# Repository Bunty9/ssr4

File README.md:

<div align="center">

# SSR4

**An open-source, four-channel 230 VAC solid-state switch for Home Assistant.**<br>
ESP32-C3 · ESPHome · zero-cross SSRs · hardware over-temperature cutoff · KiCad 10

</div>

> [!WARNING]
> **This board switches mains voltage, which can kill.** Build, test and install it only if you
> are competent to work on 230 V wiring, follow the [safety guide](docs/safety.md), and keep
> the board disconnected from mains while flashing or handling it. It is an **uncertified
> prototype design**, provided as is, without warranty.

## What it is

SSR4 turns four ordinary 230 V circuits (ceiling fans, LED lights) into Home Assistant switches.
It is small enough (90 × 75 mm) to sit in a 3D-printed case inside a wall switchboard, runs
[ESPHome](https://esphome.io) on an ESP32-C3, and works entirely on your local network.

It was designed to be **safe by construction, not by firmware**:

- **Every output turns off by itself when the board overheats.** A 60 °C temperature switch cuts
  the drive of all four SSRs in hardware, with no software in the path. The firmware adds an
  earlier 55 °C cutoff, a sensor-fault check and reporting.
- **Every output is OFF at power-up and after any reset**, enforced by gate pull-downs sized
  against the microcontroller's own reset pull-ups, before the firmware even runs, and never
  restored automatically after a power cut.
- **Mains and low voltage are 6.5 mm apart** on every layer (reinforced isolation spacing),
  checked by KiCad DRC rules shipped with the design.
- **Each channel is fused** (2 A time-lag) and has its own terminals, so the board never carries
  the sum of the loads.
- **Flash and test it from USB-C with mains disconnected**: the logic runs from USB alone.

## Gallery

| | |
|:---:|:---:|
|  |  |
| Top: mains along the upper edge, low voltage below | The terminal side: per-channel L_IN / L_OUT pairs |
|  |  |
| U7, the 60 °C hardware cutoff, sits between the SSRs | A scouter on the silkscreen: power level well over 9000 |

Full-resolution renders (4K) are in [`docs/images/`](docs/images/). The schematic and the copper
layers are in [`hardware/ssr4-schematic.pdf`](hardware/ssr4-schematic.pdf) and
[`hardware/ssr4-pcb-layers.pdf`](hardware/ssr4-pcb-layers.pdf).

## Specifications

| | |
|---|---|
| Outputs | 4 × 230 VAC, zero-cross triac SSR (Littelfuse/IXYS CPC40055ST, 20-280 Vrms, 2500 Vrms isolation) |
| Load per channel | below 1 A continuous (LED lights, fans); 2 A time-lag fuse per channel |
| Supply | 230 VAC via an isolated 5 V / 3 W module (HLK-PM01) with fuse and varistor, or USB-C 5 V for flashing |
| Controller | ESP32-C3-MINI-1 (RISC-V, Wi-Fi, 4 MB flash), native USB-C (Serial/JTAG) with ESD protection |
| Protection | hardware cutoff 60 °C ± 2 °C (TMP302, releases ~50 °C); firmware cutoff 55 °C / resume 45 °C, also latched by a hardware trip; NTC fault detection; fail-safe OFF |
| Indicators | one LED per channel, status LED |
| Board | 90 × 75 mm, 2 layers, 1.6 mm, 2 oz copper, 67 parts, four M3 holes |
| Firmware | ESPHome 2026.10 (ESP-IDF): encrypted Home Assistant API, password-protected OTA, captive-portal setup |

## From zero to switching lights

| Step | Guide |
|---|---|
| 1. Understand the board | [How it works](docs/how-it-works.md) · [Safety](docs/safety.md) |
| 2. Order it assembled (JLCPCB or PCBWay) or build it yourself | [Fabrication](docs/fabrication.md) |
| 3. Flash ESPHome over USB-C and add it to Home Assistant | [Firmware](docs/firmware.md) |
| 4. Bring it up step by step: USB, thermal checks, 24 VAC loads, first mains | [Bring-up](docs/bring-up.md) |
| 5. Wire it into a switchboard | [Installation](docs/installation.md) |
| 5b. Design a heat sink and an enclosure (STEP files included) | [Mechanical](docs/mechanical.md) |
| 6. Change it, test it, contribute | [Development](docs/development.md) · [Contributing](CONTRIBUTING.md) |

## How it has been checked

Nothing here has been built yet: rev A is a **gated, unbuilt design**. Every published file was
produced by a pipeline that refuses to release a board until its checks pass. The results of
this snapshot are in [`validation/`](validation/README.md):

| Check | Result |
|---|---|
| Datasheet pinouts: every IC, transistor, diode and connector pin extracted twice, independently, and compared | 11 parts verified, 0 disagreements left |
| Netlist tests: safety and correctness properties proved on the generated schematic | 16 passed |
| ERC | 0 errors |
| DRC, including the mains clearance and creepage rules | 0 errors, 0 unconnected (24 silkscreen warnings) |
| Fabrication rules (JLCPCB) and the order package | pass |
| Firmware behaviour on a PC simulation of the board (14 tests) | 14 passed |
| Independent design review of the final layout | 1 high and 7 medium findings: the safety-relevant ones fixed before publishing, the rest listed |
| NTC divider: closed-form design maths vs an ngspice simulation | agree within the simulator's tolerance |

Bench validation of a real board (thermal, EMC, trip points) is the next step. If you build
one, please [send a build report](https://github.com/Bunty9/ssr4/issues/new/choose).

## What it costs

About **$106 per board in parts** (5 boards, JLCPCB prices of October 2026), before PCB,
assembly and shipping. The four SSRs are $97 of that; everything else is under $9. The
[fabrication guide](docs/fabrication.md#what-it-costs) has the breakdown and a cheaper-variant
idea.

## Home Assistant

The board appears as an ESPHome device with four switches (**Channel 1-4**), the **SSR
temperature**, and three protection states: **Over-temperature**, **NTC fault** and **Hardware
over-temperature cutoff**. A channel refuses to turn on while any protection is active, so the
dashboard always shows what the hardware is really doing.

## Repository layout

```
hardware/      KiCad 10 project, libraries, circuit source (Python), fabrication files, pinouts, PDFs,
               mechanical/ (STEP assembly, board STEP, outline DXF)
firmware/      ESPHome configuration (board + PC simulation), generated pin map, tests
fwtest/        labgrid-based test harness used by the firmware tests
validation/    test results, calculations, SPICE cross-check of this snapshot
docs/          guides and full-resolution renders
```

## Contributing

Build reports, bug reports and improvements are welcome. Read [CONTRIBUTING.md](CONTRIBUTING.md)
first; safety problems go to the private channel in [SECURITY.md](SECURITY.md). This project
follows the [Contributor Covenant](CODE_OF_CONDUCT.md).

## License

- Hardware: [CERN-OHL-S-2.0](LICENSES/CERN-OHL-S-2.0.txt)
- Firmware and software: [MIT](LICENSES/MIT.txt)
- Documentation and images: [CC BY-SA 4.0](LICENSES/CC-BY-SA-4.0.txt)

Details and credits (including the scouter doodle, after fan art by camarinox; Dragon Ball ©
Bird Studio/Shueisha, Toei Animation) in [LICENSES/README.md](LICENSES/README.md).

<sub>Published from source commit `4ecfc79` on 2026-10-29.</sub>

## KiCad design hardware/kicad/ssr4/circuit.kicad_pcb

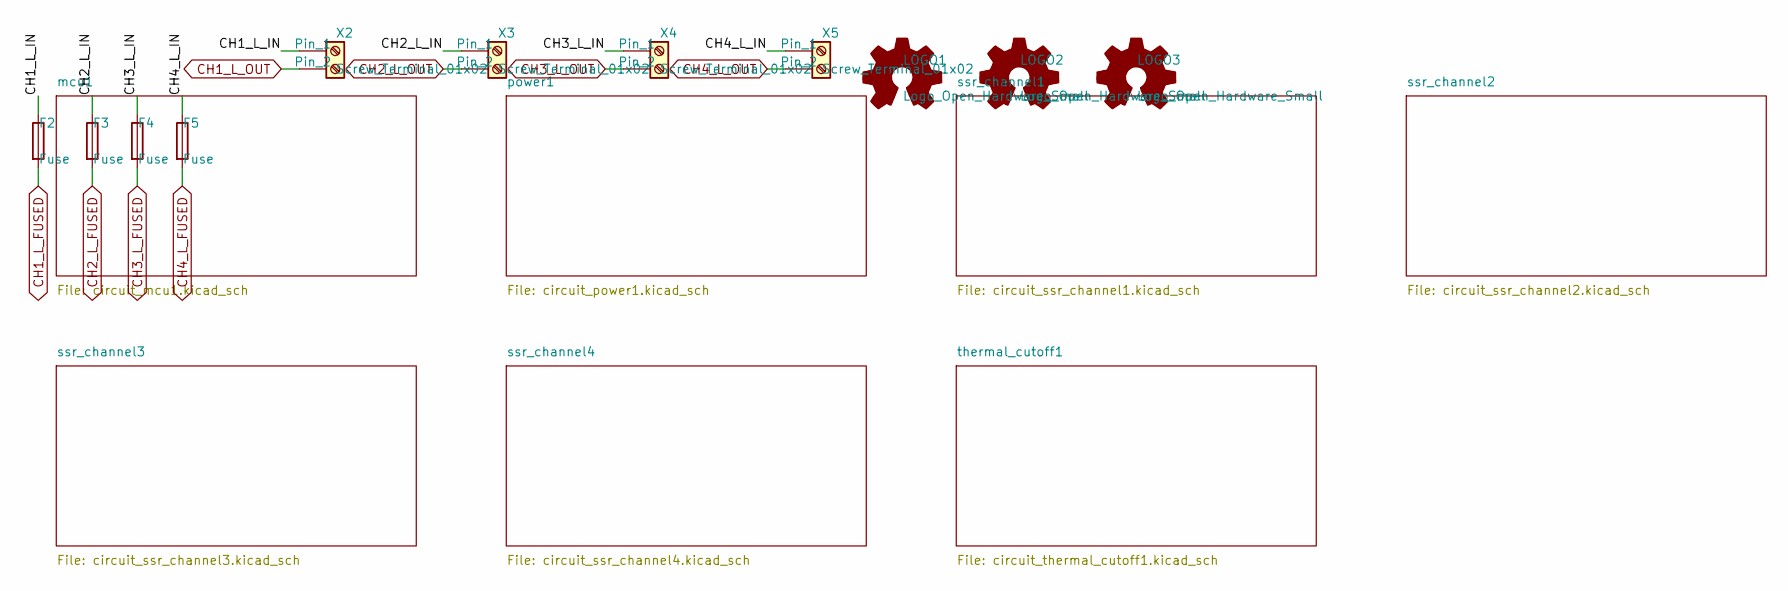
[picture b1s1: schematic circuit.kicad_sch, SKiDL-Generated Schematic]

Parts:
F2, F3, F4, F5: Fuse; Fuse_Littelfuse_395Series; MPN 39212000000; LCSC C142678
LOGO1: Logo_Open_Hardware_Small; Label_MainsWarning; MPN UNSET-MPN
LOGO2: Logo_Open_Hardware_Small; Doodle_Scouter; MPN UNSET-MPN
LOGO3: Logo_Open_Hardware_Small; Label_Terminals; MPN UNSET-MPN
X2, X3, X4, X5: Screw_Terminal_01x02; TerminalBlock_CUI_TB007-508-02_1x02_P5.08mm_Horizontal; MPN WJ500V-5.08-2P; LCSC C8465

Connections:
/CH1_L_IN: F2.1, X2.1
/CH2_L_IN: F3.1, X3.1
/CH3_L_IN: F4.1, X4.1
/CH4_L_IN: F5.1, X5.1
CH1_L_FUSED: F2.2; also elsewhere on the board
CH1_L_OUT: X2.2; also elsewhere on the board
CH2_L_FUSED: F3.2; also elsewhere on the board
CH2_L_OUT: X3.2; also elsewhere on the board
CH3_L_FUSED: F4.2; also elsewhere on the board
CH3_L_OUT: X4.2; also elsewhere on the board
CH4_L_FUSED: F5.2; also elsewhere on the board
CH4_L_OUT: X5.2; also elsewhere on the board

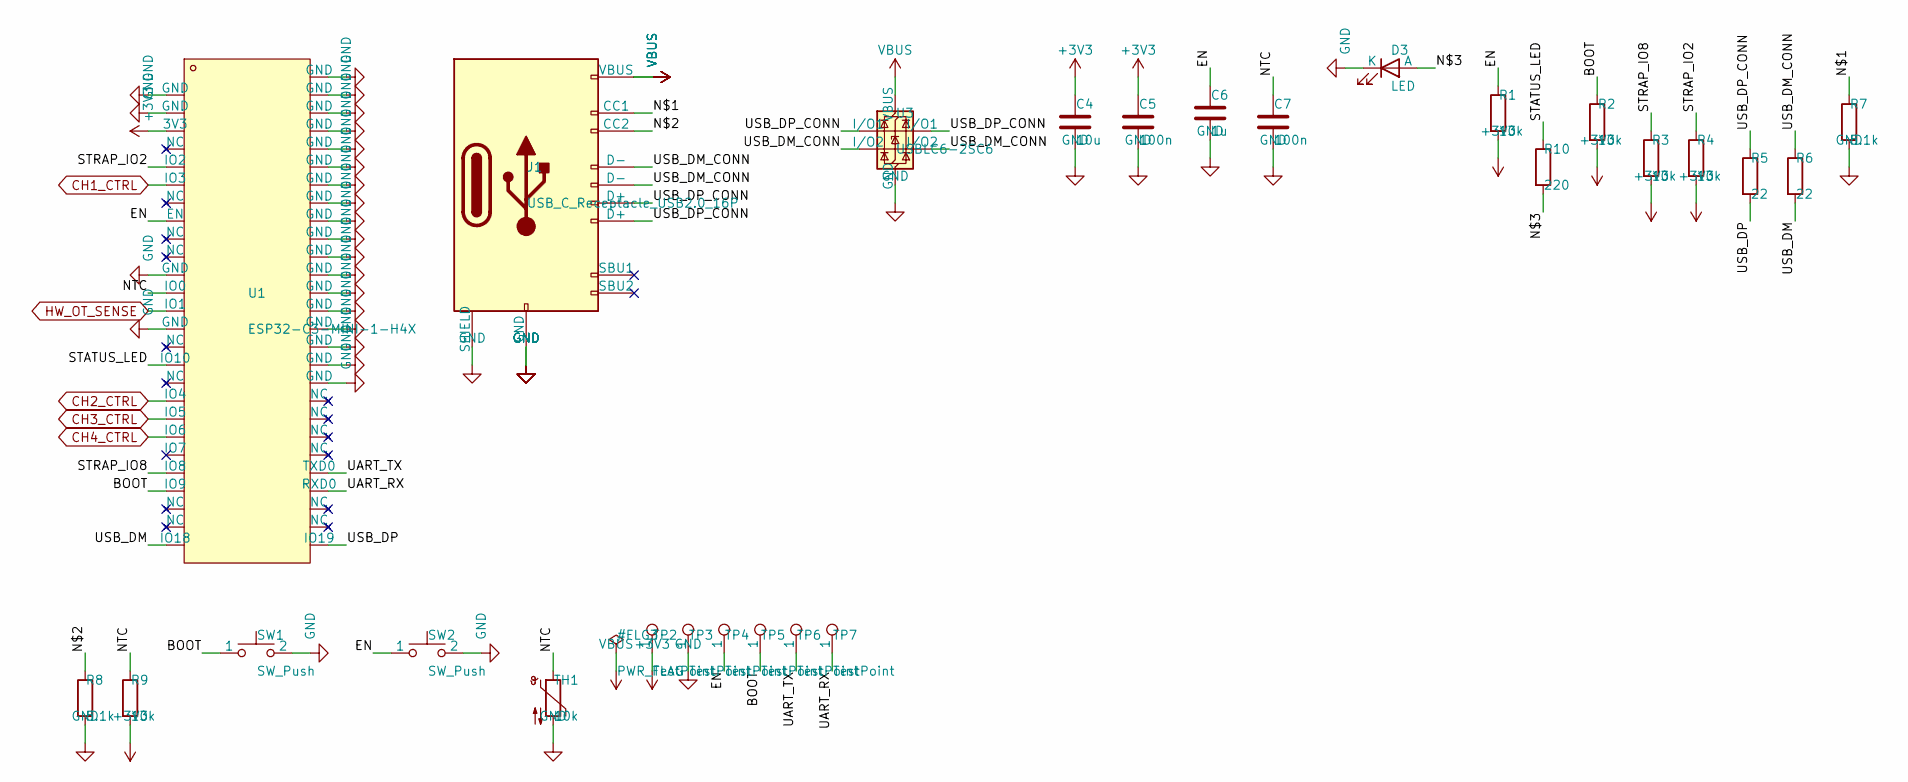
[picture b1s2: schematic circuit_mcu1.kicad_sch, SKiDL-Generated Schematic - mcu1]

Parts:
C4: 10u; C_0603_1608Metric; MPN CL10A106MA8NRNC; LCSC C96446
C5, C7: 100n; C_0402_1005Metric; MPN CL05B104KO5NNNC; LCSC C1525
C6: 1u; C_0402_1005Metric; MPN CL05A105KA5NQNC; LCSC C52923
D3: LED; LED_0603_1608Metric; MPN 19-217/R6C-AL1M2VY/6T; LCSC C2986060
J1: USB_C_Receptacle_USB2.0_16P; USB_C_Receptacle_HRO_TYPE-C-31-M-12; MPN TYPE-C-31-M-12; LCSC C165948
R1, R2, R3, R4, R9: 10k; R_0402_1005Metric; MPN 0402WGF1002TCE; LCSC C25744
R5, R6: 22; R_0402_1005Metric; MPN 0402WGF220JTCE; LCSC C25092
R7, R8: 5.1k; R_0402_1005Metric; MPN 0402WGF5101TCE; LCSC C25905
R10: 220; R_0402_1005Metric; MPN 0402WGF2200TCE; LCSC C25091
SW1, SW2: SW_Push; SW_Push_1P1T_XKB_TS-1187A; MPN TS-1187A-B-A-B; LCSC C318884
TH1: 10k; R_0603_1608Metric; MPN SDNT1608X103F3950FTF; LCSC C279936
TP2, TP3, TP4, TP5, TP6, TP7: TestPoint; TestPoint_Pad_D1.5mm; MPN UNSET-MPN
U1: ESP32-C3-MINI-1-H4X; WIFIM-SMD_ESP32-C3-MINI-1; MPN ESP32-C3-MINI-1-H4X; LCSC C41349510
U3: USBLC6-2SC6; SOT-23-6; MPN USBLC6-2SC6; LCSC C7519

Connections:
+3V3: C4.1, C5.1, R1.2, R2.2, R3.2, R4.2, R9.2, TP2.1, U1.3 (3V3); also elsewhere on the board
/mcu1/BOOT: R2.1, SW1.1, TP5.1, U1.23 (IO9)
/mcu1/EN: C6.1, R1.1, SW2.1, TP4.1, U1.8 (EN)
/mcu1/N$1: J1.A5 (CC1), R7.1
/mcu1/N$2: J1.B5 (CC2), R8.1
/mcu1/N$3: D3.2 (A), R10.2
/mcu1/NTC: C7.1, R9.1, TH1.1, U1.12 (IO0)
/mcu1/STATUS_LED: R10.1, U1.16 (IO10)
/mcu1/STRAP_IO2: R4.1, U1.5 (IO2)
/mcu1/STRAP_IO8: R3.1, U1.22 (IO8)
/mcu1/UART_RX: TP7.1, U1.30 (RXD0)
/mcu1/UART_TX: TP6.1, U1.31 (TXD0)
/mcu1/USB_DM: R6.2, U1.26 (IO18)
/mcu1/USB_DM_CONN: J1.A7 (D-), J1.B7 (D-), R6.1, U3.3 (I/O2), U3.4 (I/O2)
/mcu1/USB_DP: R5.2, U1.27 (IO19)
/mcu1/USB_DP_CONN: J1.A6 (D+), J1.B6 (D+), R5.1, U3.1 (I/O1), U3.6 (I/O1)
CH1_CTRL: U1.6 (IO3); also elsewhere on the board
CH2_CTRL: U1.18 (IO4); also elsewhere on the board
CH3_CTRL: U1.19 (IO5); also elsewhere on the board
CH4_CTRL: U1.20 (IO6); also elsewhere on the board
GND: C4.2, C5.2, C6.2, C7.2, D3.1 (K), J1.A1 (GND), J1.A12 (GND), J1.B1 (GND), J1.B12 (GND), J1.SH (SHIELD), R7.2, R8.2, SW1.2, SW2.2, TH1.2, TP3.1, U1.1 (GND), U1.2 (GND), U1.11 (GND), U1.14 (GND), U1.36 (GND), U1.37 (GND), U1.38 (GND), U1.39 (GND), U1.40 (GND), U1.41 (GND), U1.42 (GND), U1.43 (GND), U1.44 (GND), U1.45 (GND), U1.46 (GND), U1.47 (GND), U1.48 (GND), U1.49 (GND), U1.50 (GND), U1.51 (GND), U1.52 (GND), U1.53 (GND), U3.2 (GND); also elsewhere on the board
HW_OT_SENSE: U1.13 (IO1); also elsewhere on the board
VBUS: J1.A4 (VBUS), J1.A9 (VBUS), J1.B4 (VBUS), J1.B9 (VBUS), U3.5 (VBUS); also elsewhere on the board

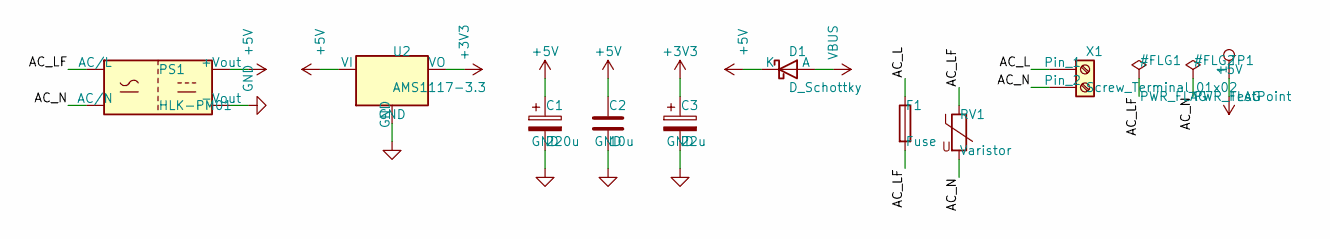
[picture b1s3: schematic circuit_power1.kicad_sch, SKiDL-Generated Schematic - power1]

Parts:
C1: 220u; CP_Elec_6.3x5.4; MPN RVT1C221M0605; LCSC C2977551
C2: 10u; C_0603_1608Metric; MPN CL10A106MA8NRNC; LCSC C96446
C3: 22u; CP_EIA-3528-21_Kemet-B; MPN CA45-B016K226T; LCSC C122226
D1: D_Schottky; D_SOD-123; MPN B5819W SL; LCSC C8598
F1: Fuse; Fuse_Littelfuse_395Series; MPN 39211000000; LCSC C99566
PS1: HLK-PM01; Converter_ACDC_Hi-Link_HLK-PMxx; MPN HLK-PM01; LCSC C209903
RV1: Varistor; RV_Disc_D12mm_W6.7mm_P7.5mm; MPN 10D561K; LCSC C2839517
TP1: TestPoint; TestPoint_Pad_D1.5mm; MPN UNSET-MPN
U2: AMS1117-3.3; SOT-223-3_TabPin2; MPN AMS1117-3.3; LCSC C6186
X1: Screw_Terminal_01x02; TerminalBlock_CUI_TB007-508-02_1x02_P5.08mm_Horizontal; MPN WJ500V-5.08-2P; LCSC C8465

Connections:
+3V3: C3.1, U2.2 (VO); also elsewhere on the board
+5V: C1.1, C2.1, D1.1 (K), PS1.4 (+Vout), TP1.1, U2.3 (VI); also elsewhere on the board
/power1/AC_L: F1.1, X1.1
/power1/AC_LF: F1.2, PS1.1 (AC/L), RV1.1
/power1/AC_N: PS1.2 (AC/N), RV1.2, X1.2
GND: C1.2, C2.2, C3.2, PS1.3 (-Vout), U2.1 (GND); also elsewhere on the board
VBUS: D1.2 (A); also elsewhere on the board

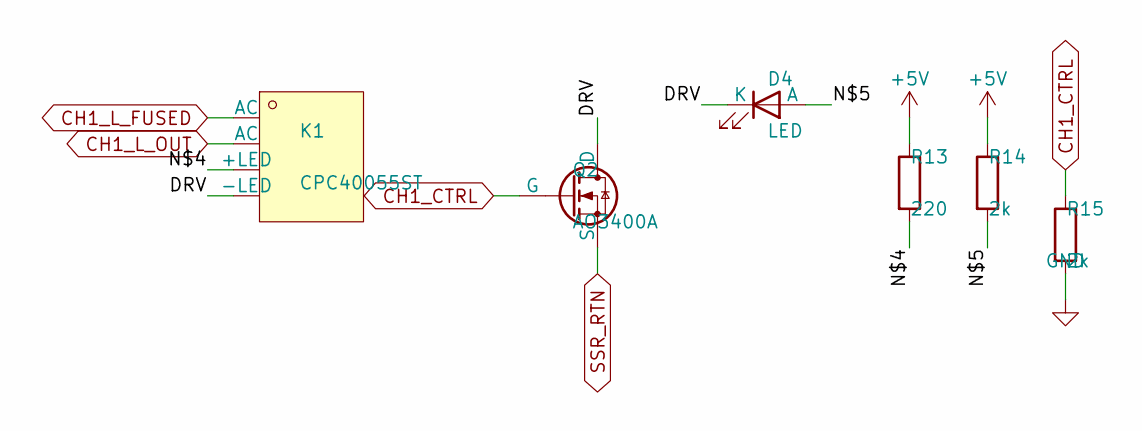
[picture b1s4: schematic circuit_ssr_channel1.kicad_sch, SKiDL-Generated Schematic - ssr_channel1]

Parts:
D4: LED; LED_0603_1608Metric; MPN 19-217/R6C-AL1M2VY/6T; LCSC C2986060
K1: CPC40055ST; SIP-4_L38.1-W3.8_CPC40055ST; MPN CPC40055ST; LCSC C1527353
Q2: AO3400A; SOT-23; MPN AO3400A; LCSC C20917
R13: 220; R_1206_3216Metric; MPN 1206W4F2200T5E; LCSC C17957
R14, R15: 2k; R_0402_1005Metric; MPN 0402WGF2001TCE; LCSC C4109

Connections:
+5V: R13.1, R14.1; also elsewhere on the board
/ssr_channel1/DRV: D4.1 (K), K1.4 (-LED), Q2.3 (D)
/ssr_channel1/N$4: K1.3 (+LED), R13.2
/ssr_channel1/N$5: D4.2 (A), R14.2
CH1_CTRL: Q2.1 (G), R15.1; also elsewhere on the board
CH1_L_FUSED: K1.1 (AC); also elsewhere on the board
CH1_L_OUT: K1.2 (AC); also elsewhere on the board
GND: R15.2; also elsewhere on the board
SSR_RTN: Q2.2 (S); also elsewhere on the board

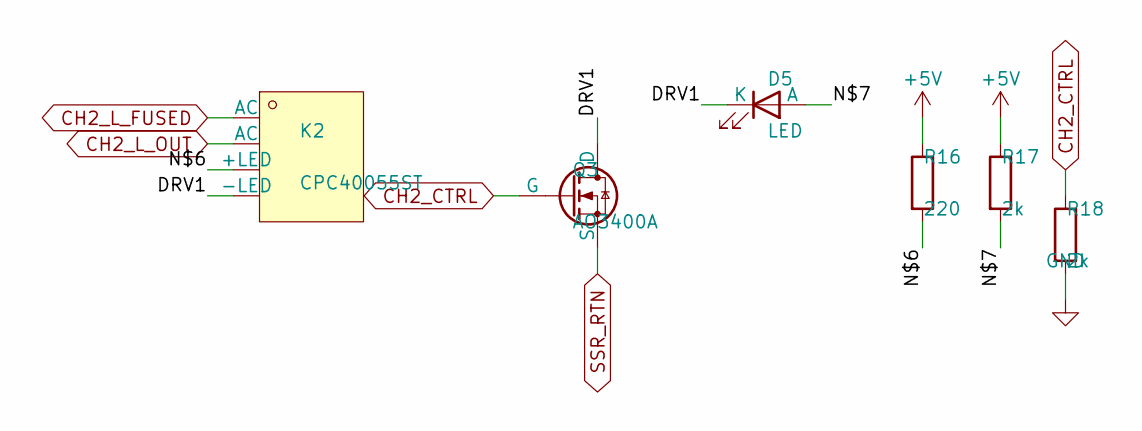
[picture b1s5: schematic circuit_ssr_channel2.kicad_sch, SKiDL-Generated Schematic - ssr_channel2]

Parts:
D5: LED; LED_0603_1608Metric; MPN 19-217/R6C-AL1M2VY/6T; LCSC C2986060
K2: CPC40055ST; SIP-4_L38.1-W3.8_CPC40055ST; MPN CPC40055ST; LCSC C1527353
Q3: AO3400A; SOT-23; MPN AO3400A; LCSC C20917
R16: 220; R_1206_3216Metric; MPN 1206W4F2200T5E; LCSC C17957
R17, R18: 2k; R_0402_1005Metric; MPN 0402WGF2001TCE; LCSC C4109

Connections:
+5V: R16.1, R17.1; also elsewhere on the board
/ssr_channel2/DRV1: D5.1 (K), K2.4 (-LED), Q3.3 (D)
/ssr_channel2/N$6: K2.3 (+LED), R16.2
/ssr_channel2/N$7: D5.2 (A), R17.2
CH2_CTRL: Q3.1 (G), R18.1; also elsewhere on the board
CH2_L_FUSED: K2.1 (AC); also elsewhere on the board
CH2_L_OUT: K2.2 (AC); also elsewhere on the board
GND: R18.2; also elsewhere on the board
SSR_RTN: Q3.2 (S); also elsewhere on the board

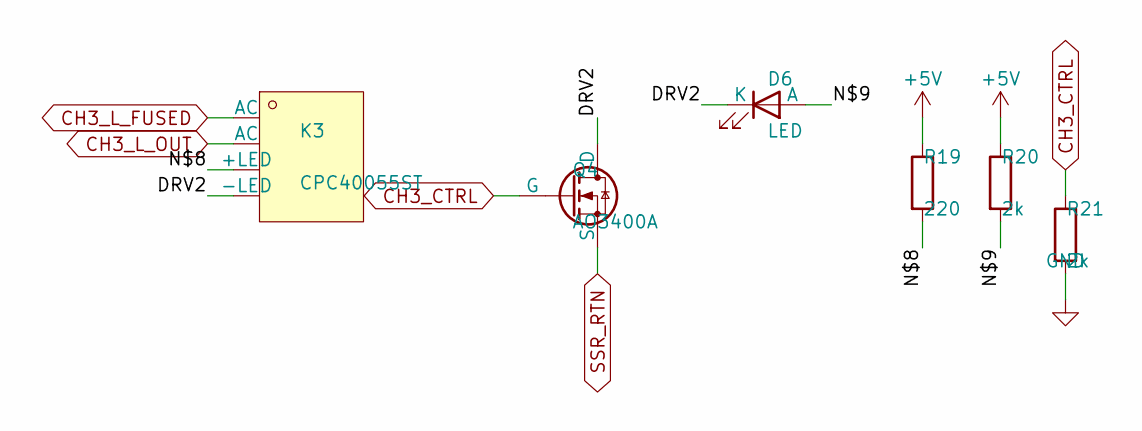
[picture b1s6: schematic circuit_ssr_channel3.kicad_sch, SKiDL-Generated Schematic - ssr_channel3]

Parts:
D6: LED; LED_0603_1608Metric; MPN 19-217/R6C-AL1M2VY/6T; LCSC C2986060
K3: CPC40055ST; SIP-4_L38.1-W3.8_CPC40055ST; MPN CPC40055ST; LCSC C1527353
Q4: AO3400A; SOT-23; MPN AO3400A; LCSC C20917
R19: 220; R_1206_3216Metric; MPN 1206W4F2200T5E; LCSC C17957
R20, R21: 2k; R_0402_1005Metric; MPN 0402WGF2001TCE; LCSC C4109

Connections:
+5V: R19.1, R20.1; also elsewhere on the board
/ssr_channel3/DRV2: D6.1 (K), K3.4 (-LED), Q4.3 (D)
/ssr_channel3/N$8: K3.3 (+LED), R19.2
/ssr_channel3/N$9: D6.2 (A), R20.2
CH3_CTRL: Q4.1 (G), R21.1; also elsewhere on the board
CH3_L_FUSED: K3.1 (AC); also elsewhere on the board
CH3_L_OUT: K3.2 (AC); also elsewhere on the board
GND: R21.2; also elsewhere on the board
SSR_RTN: Q4.2 (S); also elsewhere on the board

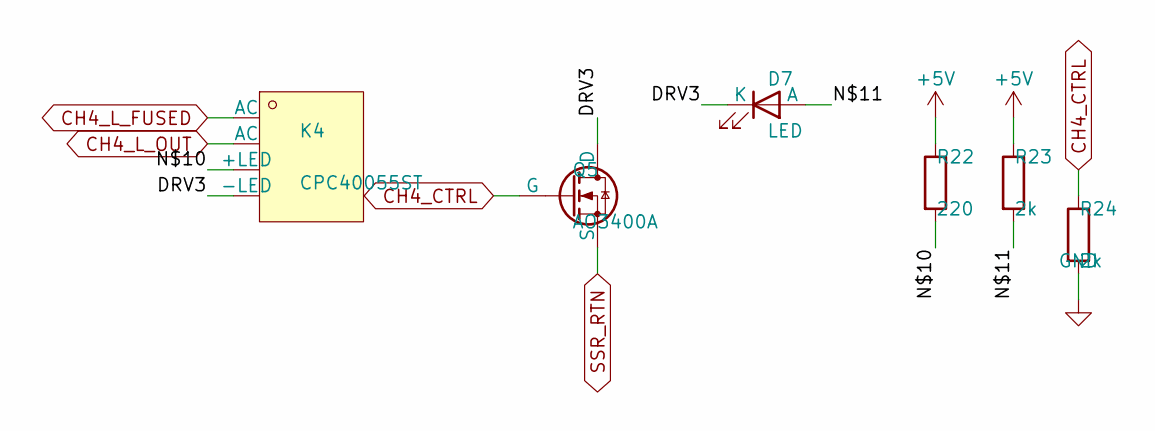
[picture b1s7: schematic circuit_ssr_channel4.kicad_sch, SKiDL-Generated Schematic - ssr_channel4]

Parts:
D7: LED; LED_0603_1608Metric; MPN 19-217/R6C-AL1M2VY/6T; LCSC C2986060
K4: CPC40055ST; SIP-4_L38.1-W3.8_CPC40055ST; MPN CPC40055ST; LCSC C1527353
Q5: AO3400A; SOT-23; MPN AO3400A; LCSC C20917
R22: 220; R_1206_3216Metric; MPN 1206W4F2200T5E; LCSC C17957
R23, R24: 2k; R_0402_1005Metric; MPN 0402WGF2001TCE; LCSC C4109

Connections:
+5V: R22.1, R23.1; also elsewhere on the board
/ssr_channel4/DRV3: D7.1 (K), K4.4 (-LED), Q5.3 (D)
/ssr_channel4/N$10: K4.3 (+LED), R22.2
/ssr_channel4/N$11: D7.2 (A), R23.2
CH4_CTRL: Q5.1 (G), R24.1; also elsewhere on the board
CH4_L_FUSED: K4.1 (AC); also elsewhere on the board
CH4_L_OUT: K4.2 (AC); also elsewhere on the board
GND: R24.2; also elsewhere on the board
SSR_RTN: Q5.2 (S); also elsewhere on the board

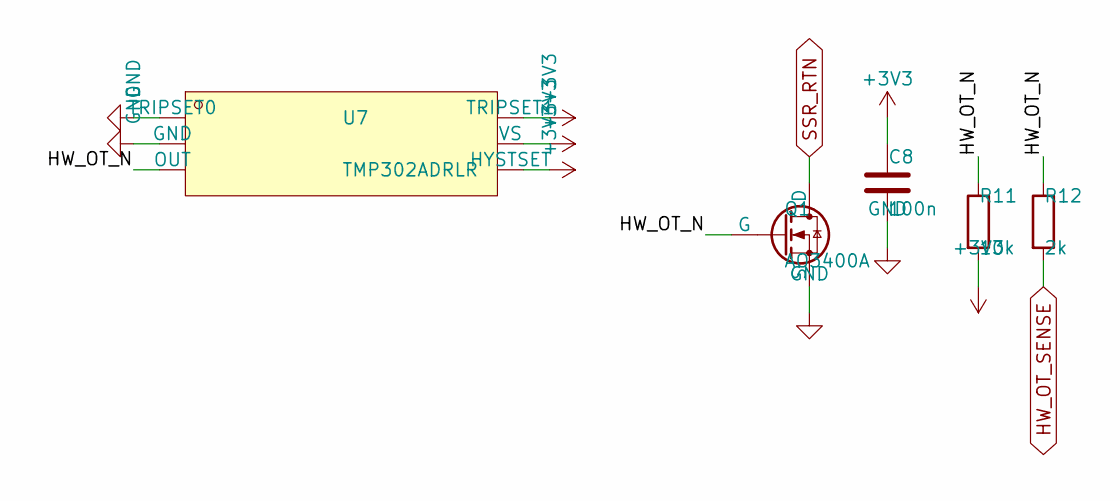
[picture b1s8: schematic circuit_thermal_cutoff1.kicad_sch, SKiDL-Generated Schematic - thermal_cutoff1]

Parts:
C8: 100n; C_0402_1005Metric; MPN CL05B104KO5NNNC; LCSC C1525
Q1: AO3400A; SOT-23; MPN AO3400A; LCSC C20917
R11: 10k; R_0402_1005Metric; MPN 0402WGF1002TCE; LCSC C25744
R12: 2k; R_0402_1005Metric; MPN 0402WGF2001TCE; LCSC C4109
U7: TMP302ADRLR; SOT-563_TI_DRL0006A; MPN TMP302ADRLR; LCSC C2877557

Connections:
+3V3: C8.1, R11.2, U7.4 (HYSTSET), U7.5 (VS), U7.6 (TRIPSET1); also elsewhere on the board
/thermal_cutoff1/HW_OT_N: Q1.1 (G), R11.1, R12.1, U7.3 (OUT)
GND: C8.2, Q1.2 (S), U7.1 (TRIPSET0), U7.2 (GND); also elsewhere on the board
HW_OT_SENSE: R12.2; also elsewhere on the board
SSR_RTN: Q1.3 (D); also elsewhere on the board

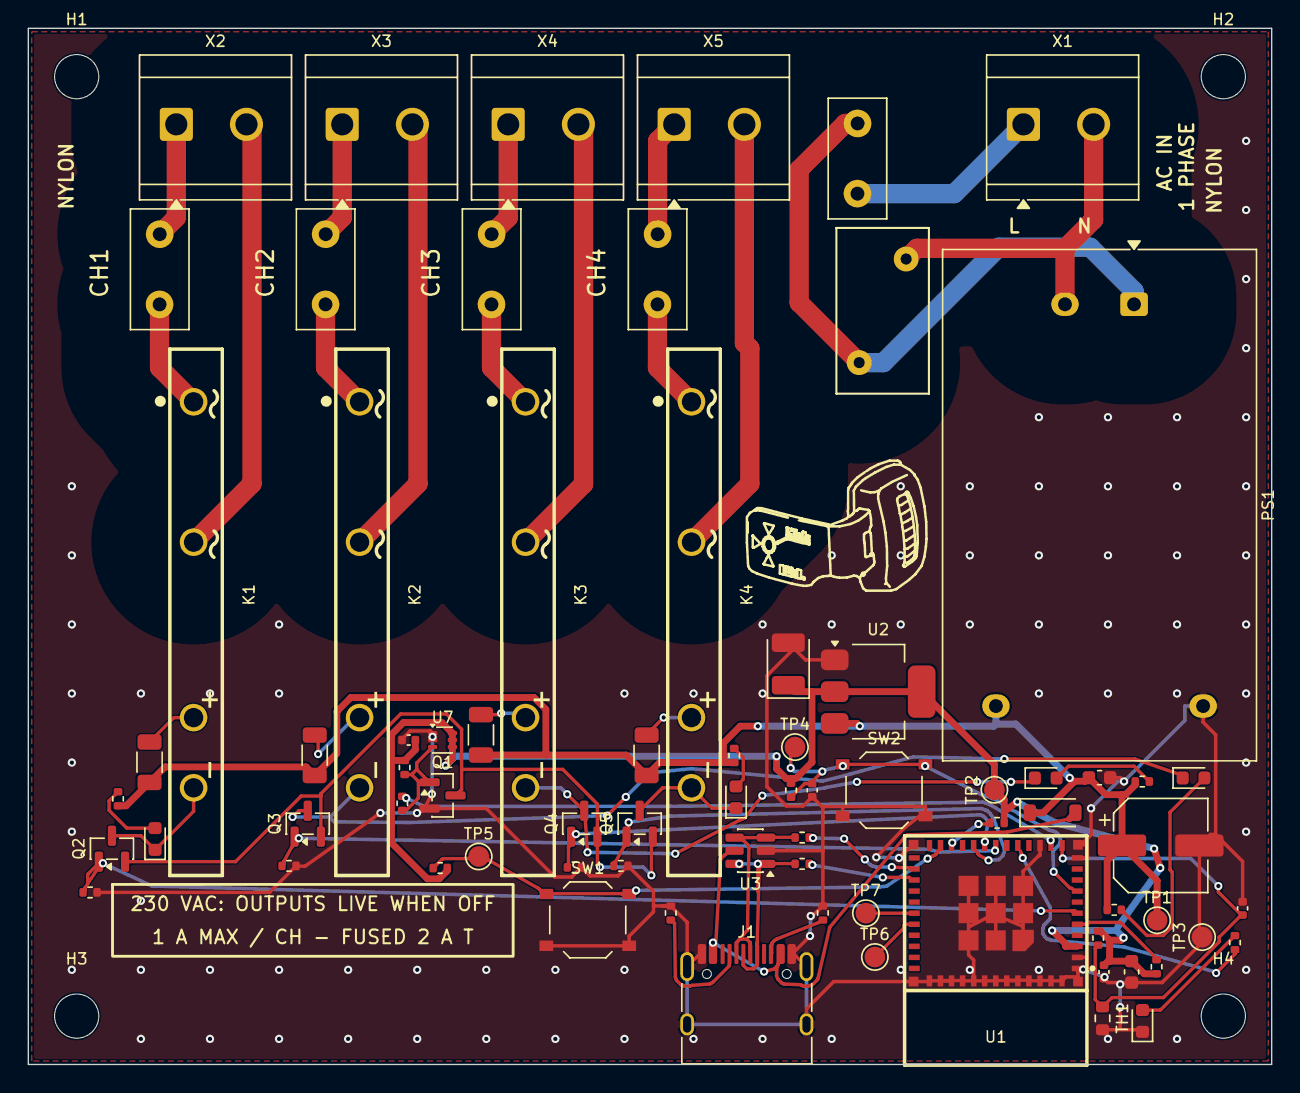
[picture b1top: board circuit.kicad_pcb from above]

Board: 2 copper layers, 90.0 x 75.0 mm, 81 parts (0 on the bottom side), 53 nets.

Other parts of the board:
H1, H2, H3, H4: MountingHole; MountingHole_3.2mm_M3

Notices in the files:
README.md:
Docs: CC BY-SA 4.0
parts and their libraries:
Silkscreen doodle: scouter line art, 13.0 x 9.5 mm, silkscreen only, no copper. Traced from fan art of the Dragon Ball Z scouter (camarinox, DeviantArt); Dragon Ball is (c) Bird Studio/Shueisha, Toei Animation. Personal decoration: not covered by this repo hardware licence.
